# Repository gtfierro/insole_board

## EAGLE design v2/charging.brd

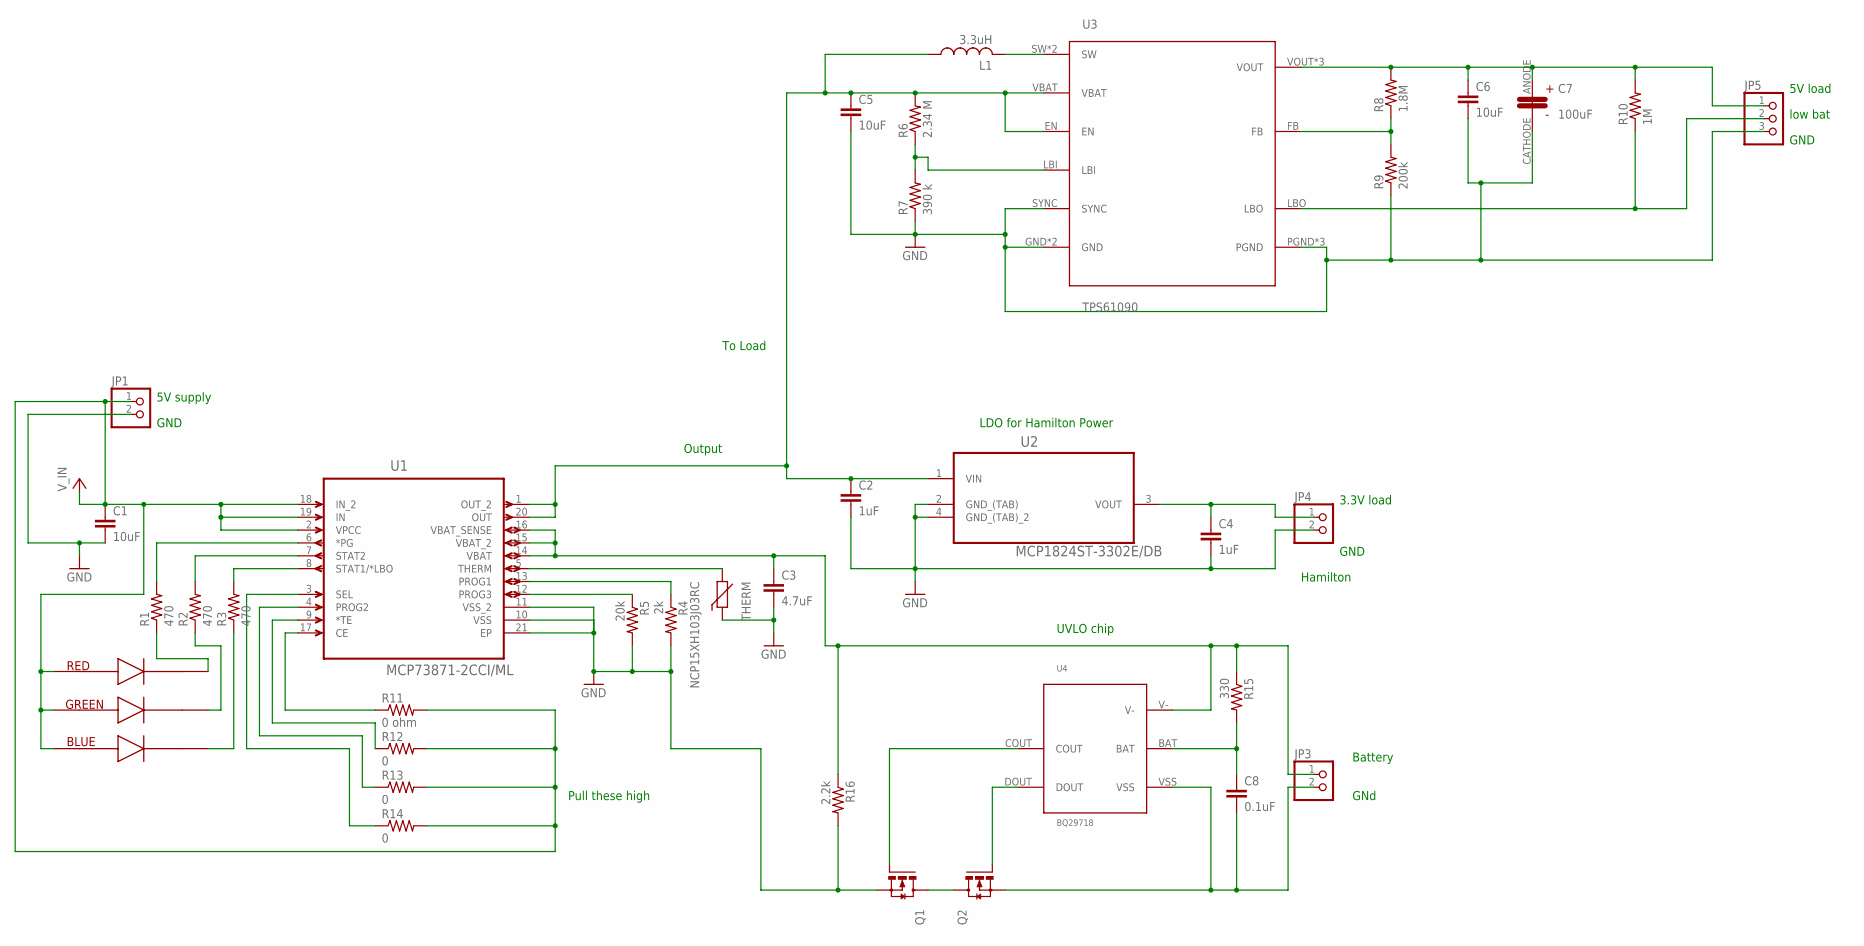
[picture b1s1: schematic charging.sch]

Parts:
C1: 10uF; C0805
C2, C4: 1uF; C0603K
C3: 4.7uF; C0805
C5, C6: 10uF; C0603K
C7: 100uF; 6032
C8: 0.1uF; C0805
JP1, JP3, JP4: PINHD-1X2; 1X02
JP5: PINHD-1X3; 1X03
L1: 3.3uH; 2-SMD
Q1, Q2: CSD16301Q2; 6-SMD
R1, R2, R3: 470; R0805
R4: 2k; R0805
R5: 20k; R0805
R6: 2.34 M; R0603
R7: 390 k; R0603
R8: 1.8M; R0603
R9: 200k; R0603
R10: 1M; R0603
R11: 0 ohm; R0603
R12, R13, R14: 0; R0603
R15: 330; R0805
R16: 2.2k; R0805
THERM: NCP15XH103J03RC; CT/CN0402
U1: MCP73871-2CCI/ML; QFN50P400X400X100-21N
U2: MCP1824ST-3302E/DB; SOT230P700X180-4N
U3: TPS61090; QFN-16
U4: BQ29718; 6-WFDFN
U$1: CLP6C-FKB; CREE_PLCC6_3-IN-1_SMD_LED_CLP6C-FKB

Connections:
GND: C1.2, C2.2, C3.2, C4.2, C5.2, C6.2, C7.CATHODE, JP1.2, JP4.2, JP5.3, Q1.S_1 (S), Q1.S_2 (S), R4.2, R5.2, R7.1, R9.1, R16.2, THERM.1, U1.10 (VSS), U1.11 (VSS_2), U1.21 (EP), U2.2 (GND_(TAB)), U2.4 (GND_(TAB)_2), U3.GND, U3.P$17 (GND), U3.PGND, U3.PGND_2 (PGND), U3.PGND_3 (PGND), U3.SYNC
unnamed: R3.2, U1.8 (STAT1/*LBO)
unnamed: R2.2, U1.7 (STAT2)
unnamed: R1.2, U1.6 (*PG)
unnamed: R1.1, U$1.RED_CATHODE
unnamed: R2.1, U$1.GREEN_CATHODE
unnamed: R3.1, U$1.BLUE_CATHODE
unnamed: R11.1, U1.17 (CE)
unnamed: R12.1, U1.9 (*TE)
unnamed: R13.1, U1.4 (PROG2)
unnamed: R14.1, U1.3 (SEL)
unnamed: C2.1, C5.1, L1.P$1 (1), R6.2, U1.1 (OUT_2), U1.20 (OUT), U2.1 (VIN), U3.EN, U3.VBAT
unnamed: THERM.2, U1.5 (THERM)
unnamed: R4.1, U1.13 (PROG1)
unnamed: Q2.G, U4.DOUT
unnamed: R5.1, U1.12 (PROG3)
unnamed: C4.1, JP4.1, U2.3 (VOUT)
unnamed: R6.1, R7.2, U3.LBI
unnamed: L1.P$2 (2), U3.SW, U3.SW_2 (SW)
unnamed: C6.1, C7.ANODE, JP5.1, R8.2, R10.2, U3.VOUT, U3.VOUT_2 (VOUT), U3.VOUT_3 (VOUT)
unnamed: R8.1, R9.2, U3.FB
unnamed: Q1.G, U4.COUT
unnamed: JP5.2, R10.1, U3.LBO
unnamed: Q1.D_1 (D), Q1.D_2 (D), Q1.D_3 (D), Q1.D_4 (D), Q1.D_5 (D), Q2.D_1 (D), Q2.D_2 (D), Q2.D_3 (D), Q2.D_4 (D), Q2.D_5 (D)
unnamed: C8.2, JP3.2, Q2.S_1 (S), Q2.S_2 (S), U4.VSS
unnamed: C3.1, JP3.1, R15.1, R16.1, U1.14 (VBAT), U1.15 (VBAT_2), U1.16 (VBAT_SENSE), U4.V-
unnamed: C8.1, R15.2, U4.BAT
VCC: C1.1, JP1.1, R11.2, R12.2, R13.2, R14.2, U1.2 (VPCC), U1.18 (IN_2), U1.19 (IN), U$1.BLUE_ANODE, U$1.GREEN_ANODE, U$1.RED_ANODE

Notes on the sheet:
Output
Battery
Hamilton
LDO for Hamilton Power
To Load
5V load
low bat
GND
3.3V load
GNd
5V supply
Pull these high
UVLO chip

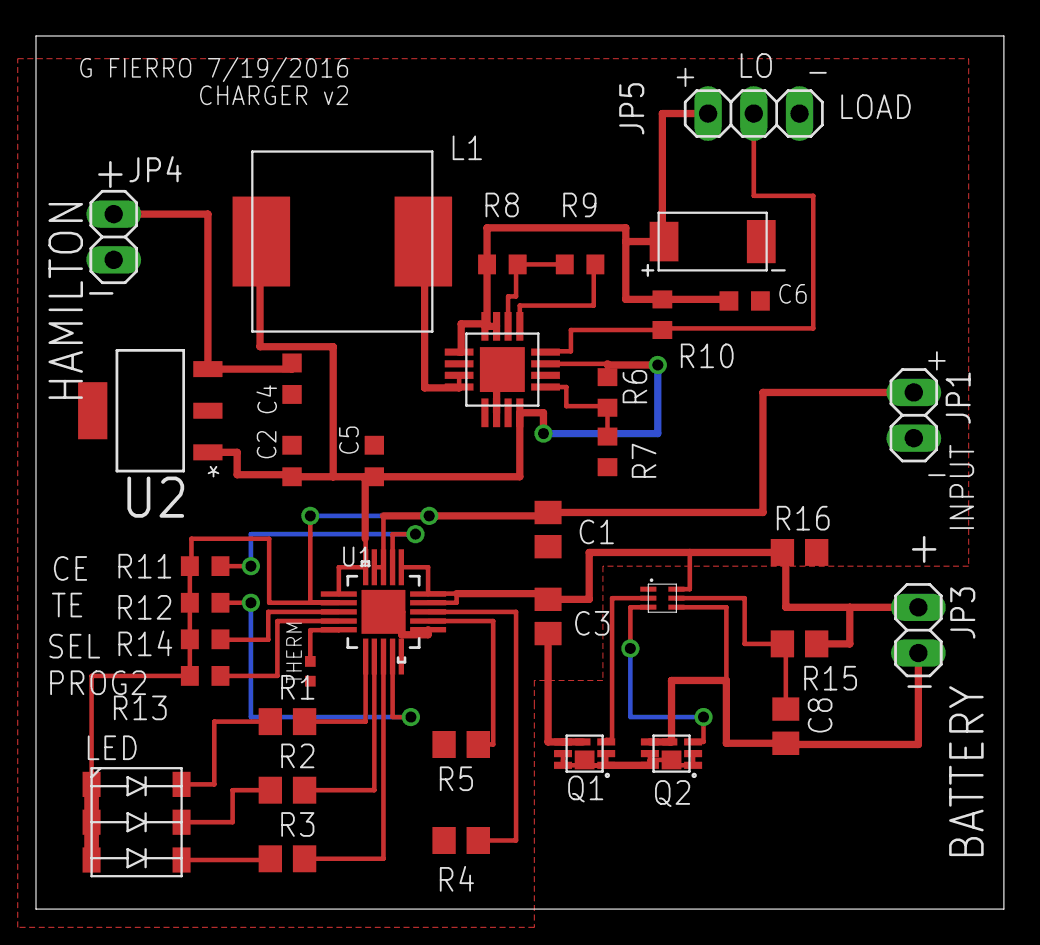
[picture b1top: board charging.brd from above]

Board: 2 copper layers, 53.8 x 48.5 mm, 37 parts (0 on the bottom side), 28 nets.

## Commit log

2016-07-19 add insole library
2016-07-19 add schematics
